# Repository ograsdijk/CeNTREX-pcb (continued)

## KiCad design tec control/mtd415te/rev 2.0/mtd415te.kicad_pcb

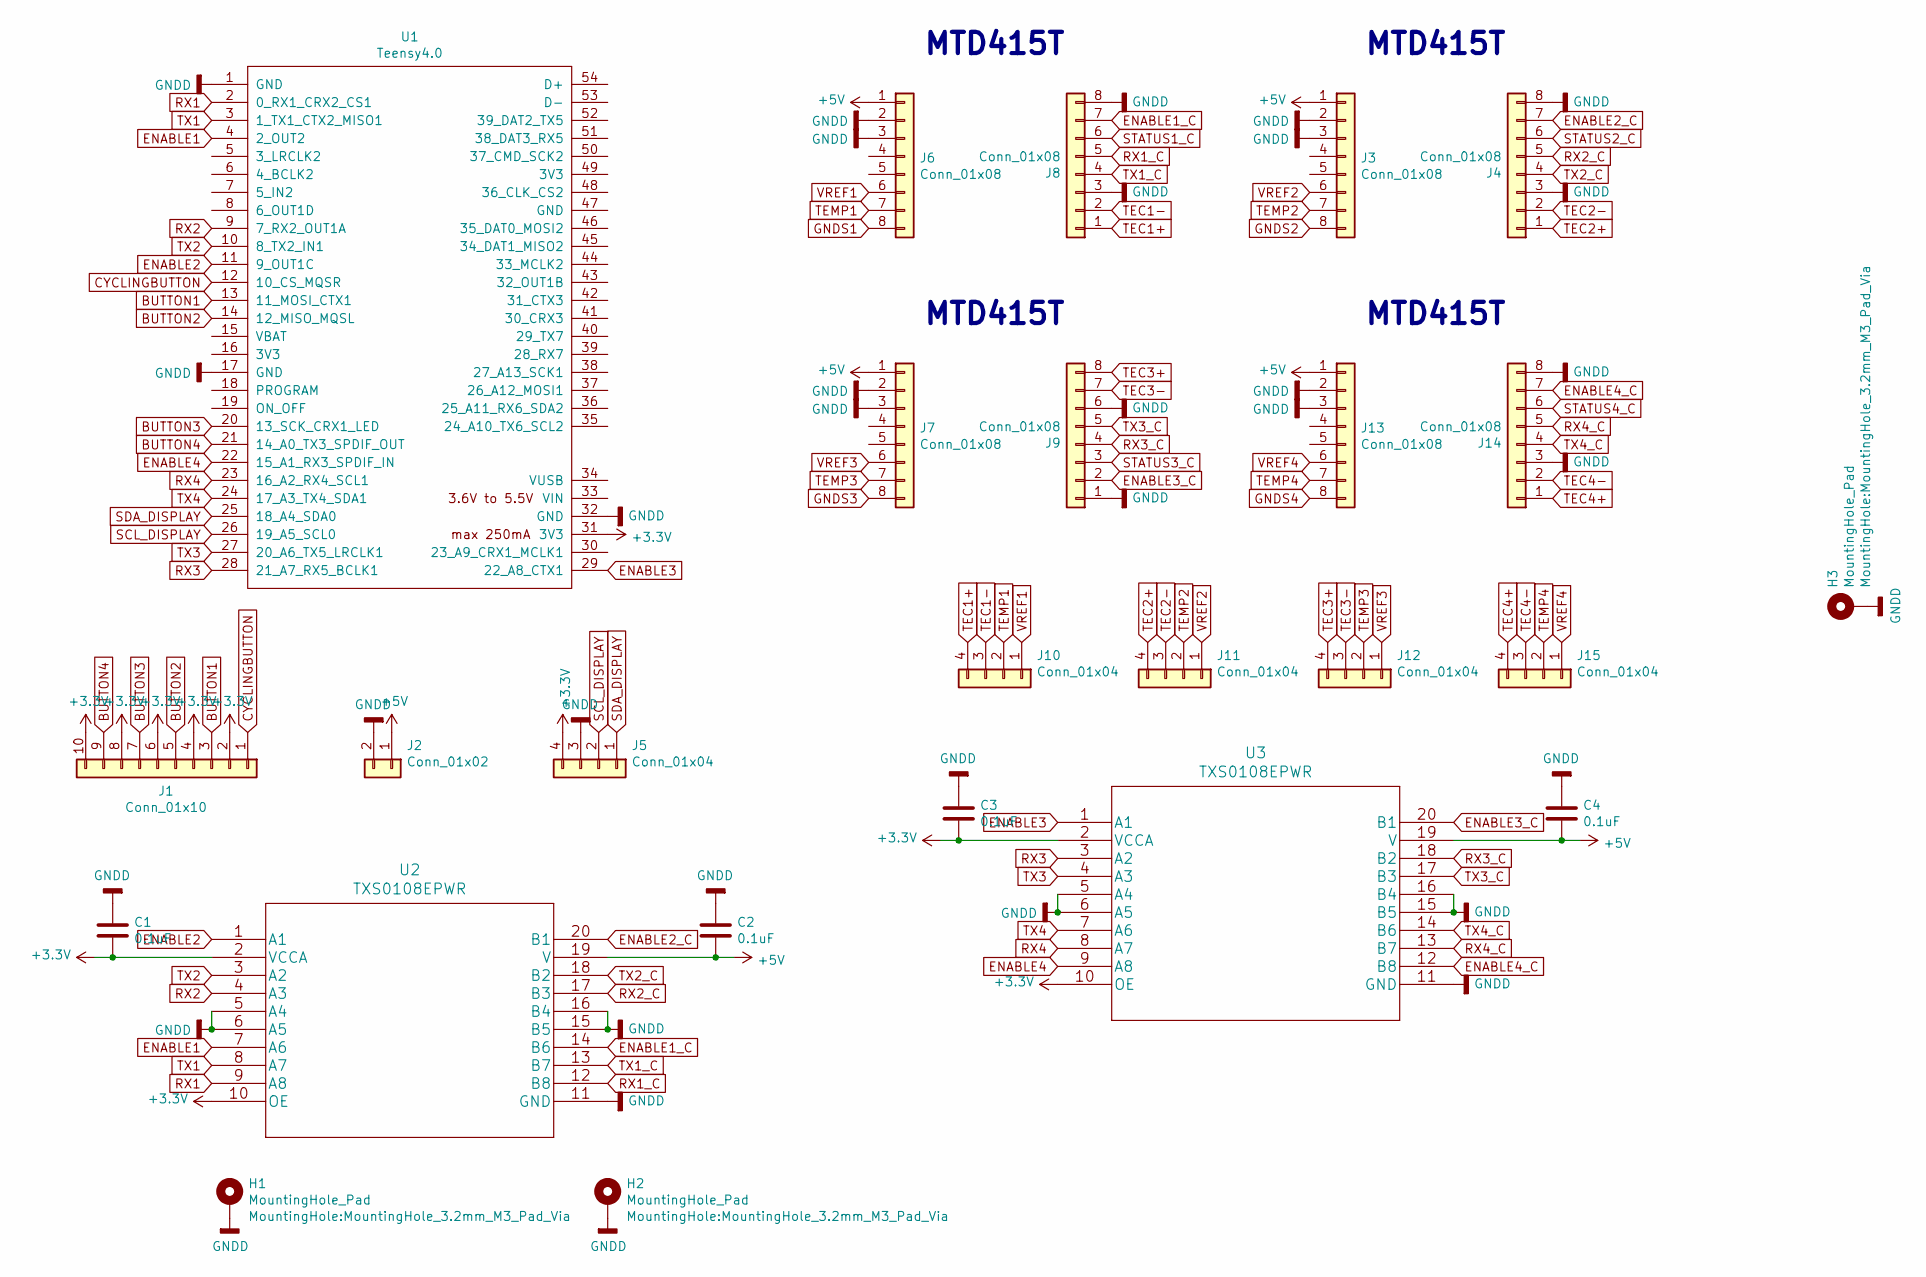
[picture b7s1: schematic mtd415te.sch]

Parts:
C1, C2, C3, C4: 0.1uF; C_0603_1608Metric
H1, H2, H3: MountingHole_Pad; MountingHole_3.2mm_M3_Pad_Via
J1: Conn_01x10; PinHeader_1x10_P2.54mm_Vertical
J2: Conn_01x02; TerminalBlock_RND_205-00001_1x02_P5.00mm_Horizontal
J3, J4, J6, J7, J8, J9, J13, J14: Conn_01x08; PinHeader_1x08_P2.54mm_Vertical
J5: Conn_01x04; PinHeader_1x04_P2.54mm_Vertical
J10, J11, J12, J15: Conn_01x04; TerminalBlock_RND_205-00003_1x04_P5.00mm_Horizontal
U1: Teensy4.0; Teensy40
U2, U3: TXS0108EPWR

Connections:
+3V3: C1.2, C3.2, J1.2, J1.4, J1.6, J1.8, J1.10, J5.4, U1.31 (3V3), U2.2 (VCCA), U2.10 (OE), U3.2 (VCCA), U3.10 (OE)
+5V: C2.2, C4.2, J2.1, J3.1, J6.1, J7.1, J13.1, U2.19 (V), U3.19 (V)
BUTTON1: J1.3, U1.13 (11_MOSI_CTX1)
BUTTON2: J1.5, U1.14 (12_MISO_MQSL)
BUTTON3: J1.7, U1.20 (13_SCK_CRX1_LED)
BUTTON4: J1.9, U1.21 (14_A0_TX3_SPDIF_OUT)
CYCLINGBUTTON: J1.1, U1.12 (10_CS_MQSR)
ENABLE1: U1.4 (2_OUT2), U2.7 (A6)
ENABLE1_C: J8.7, U2.14 (B6)
ENABLE2: U1.11 (9_OUT1C), U2.1 (A1)
ENABLE2_C: J4.7, U2.20 (B1)
ENABLE3: U1.29 (22_A8_CTX1), U3.1 (A1)
ENABLE3_C: J9.2, U3.20 (B1)
ENABLE4: U1.22 (15_A1_RX3_SPDIF_IN), U3.9 (A8)
ENABLE4_C: J14.7, U3.12 (B8)
GNDD: C1.1, C2.1, C3.1, C4.1, H1.1, H2.1, H3.1, J2.2, J3.2, J3.3, J4.3, J4.8, J5.3, J6.2, J6.3, J7.2, J7.3, J8.3, J8.8, J9.1, J9.6, J13.2, J13.3, J14.3, J14.8, U1.1 (GND), U1.17 (GND), U1.32 (GND), U2.5 (A4), U2.6 (A5), U2.11 (GND), U2.15 (B5), U2.16 (B4), U3.5 (A4), U3.6 (A5), U3.11 (GND), U3.15 (B5), U3.16 (B4)
GNDS1: J6.8
GNDS2: J3.8
GNDS3: J7.8
GNDS4: J13.8
RX1: U1.2 (0_RX1_CRX2_CS1), U2.9 (A8)
RX1_C: J8.5, U2.12 (B8)
RX2: U1.9 (7_RX2_OUT1A), U2.4 (A3)
RX2_C: J4.5, U2.17 (B3)
RX3: U1.28 (21_A7_RX5_BCLK1), U3.3 (A2)
RX3_C: J9.4, U3.18 (B2)
RX4: U1.23 (16_A2_RX4_SCL1), U3.8 (A7)
RX4_C: J14.5, U3.13 (B7)
SCL_DISPLAY: J5.2, U1.26 (19_A5_SCL0)
SDA_DISPLAY: J5.1, U1.25 (18_A4_SDA0)
STATUS1_C: J8.6
STATUS2_C: J4.6
STATUS3_C: J9.3
STATUS4_C: J14.6
TEC1+: J8.1, J10.4
TEC1-: J8.2, J10.3
TEC2+: J4.1, J11.4
TEC2-: J4.2, J11.3
TEC3+: J9.8, J12.4
TEC3-: J9.7, J12.3
TEC4+: J14.1, J15.4
TEC4-: J14.2, J15.3
TEMP1: J6.7, J10.2
TEMP2: J3.7, J11.2
TEMP3: J7.7, J12.2
TEMP4: J13.7, J15.2
TX1: U1.3 (1_TX1_CTX2_MISO1), U2.8 (A7)
TX1_C: J8.4, U2.13 (B7)
TX2: U1.10 (8_TX2_IN1), U2.3 (A2)
TX2_C: J4.4, U2.18 (B2)
TX3: U1.27 (20_A6_TX5_LRCLK1), U3.4 (A3)
TX3_C: J9.5, U3.17 (B3)
TX4: U1.24 (17_A3_TX4_SDA1), U3.7 (A6)
TX4_C: J14.4, U3.14 (B6)
VREF1: J6.6, J10.1
VREF2: J3.6, J11.1
VREF3: J7.6, J12.1
VREF4: J13.6, J15.1

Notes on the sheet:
MTD415T

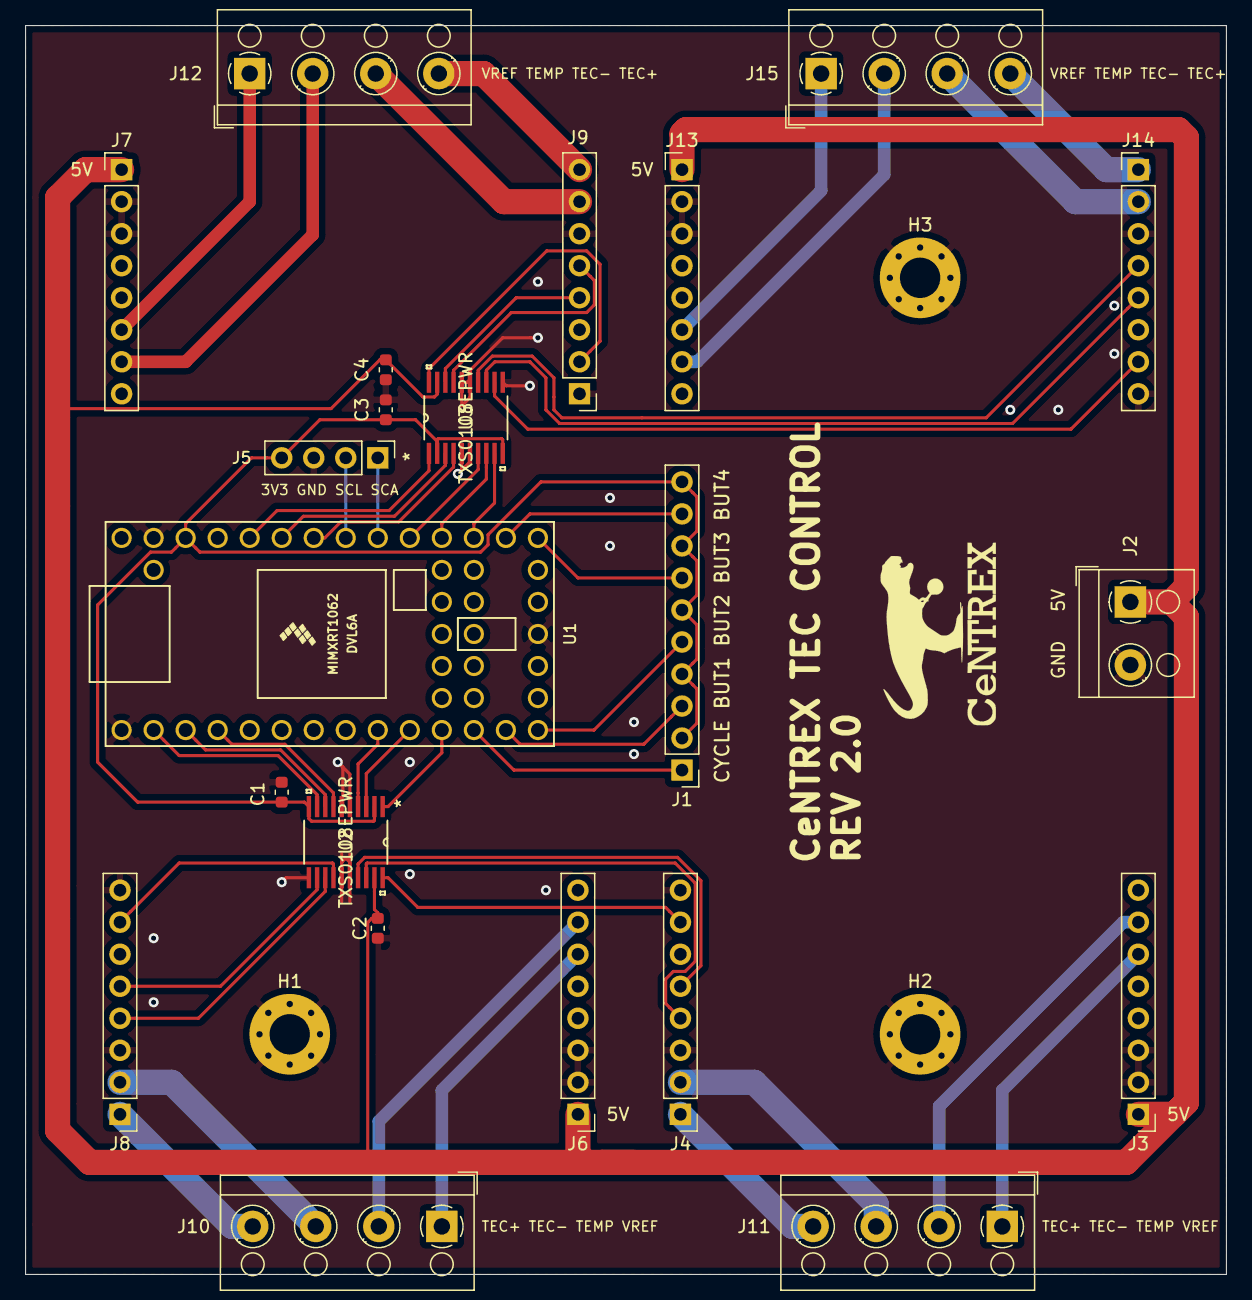
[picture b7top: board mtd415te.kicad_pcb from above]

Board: 2 copper layers, 95.3 x 99.1 mm, 26 parts (0 on the bottom side), 50 nets.

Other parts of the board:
 : CeNTREX logo
